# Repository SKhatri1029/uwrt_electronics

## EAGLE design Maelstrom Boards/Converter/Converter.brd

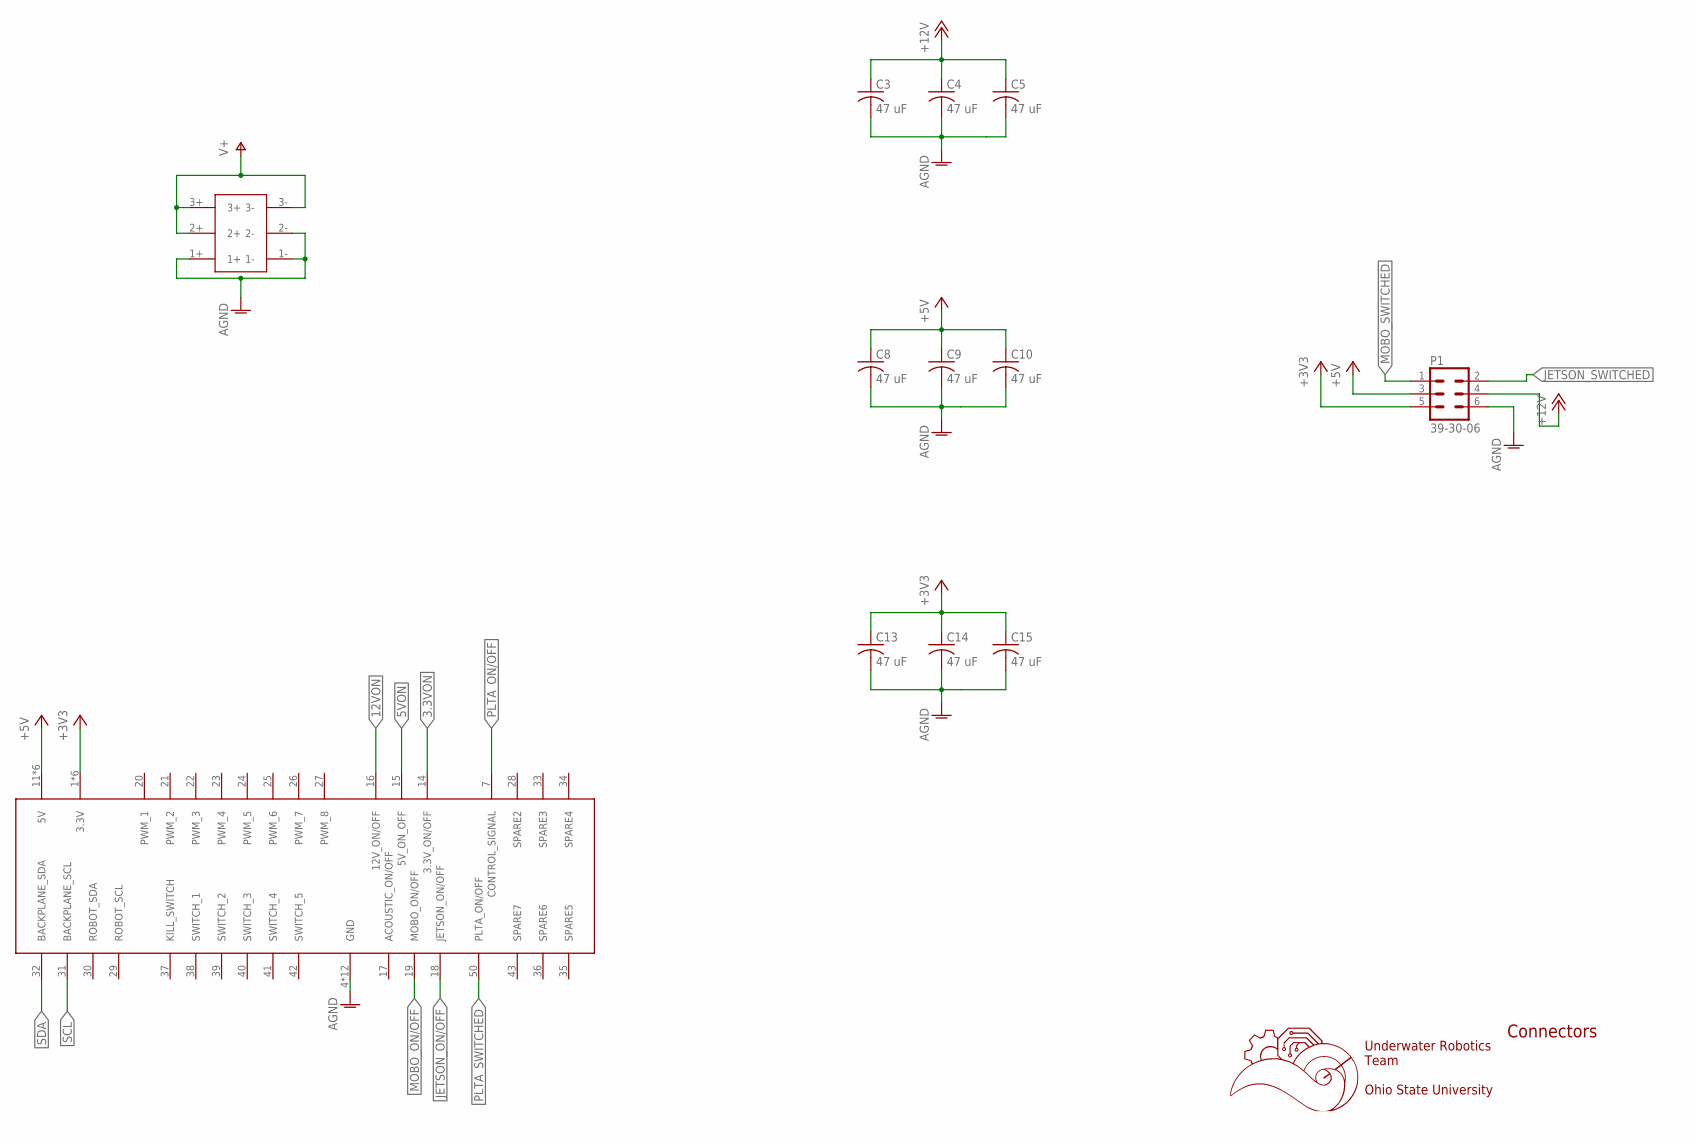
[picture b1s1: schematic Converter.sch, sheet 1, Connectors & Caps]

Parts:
C3, C4, C5, C8, C9, C10, C13, C14, C15: 47 uF; C1206K
P1: 39-30-06; 39-30-?06?
U$1: 5530843-EDGE; 5530843-6-BOARDFINGERS
U$3: 6PIN-VERT; 6PIN_VERT

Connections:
3.3VON: U$1.14 (3.3V_ON/OFF); also elsewhere on the board
5VON: U$1.15 (5V_ON_OFF); also elsewhere on the board
12VON: U$1.16 (12V_ON/OFF); also elsewhere on the board
+3V3: C13.1, C14.1, C15.1, P1.5, U$1.1 (3.3V), U$1.2 (3.3V), U$1.3 (3.3V), U$1.54 (3.3V), U$1.55 (3.3V), U$1.56 (3.3V); also elsewhere on the board
+5V: C8.1, C9.1, C10.1, P1.3, U$1.11 (5V), U$1.12 (5V), U$1.13 (5V), U$1.44 (5V), U$1.45 (5V), U$1.46 (5V); also elsewhere on the board
+12V: C3.1, C4.1, C5.1, P1.4; also elsewhere on the board
AGND: C3.2, C4.2, C5.2, C8.2, C9.2, C10.2, C13.2, C14.2, C15.2, P1.6, U$1.4 (GND), U$1.5 (GND), U$1.6 (GND), U$1.8 (GND), U$1.9 (GND), U$1.10 (GND), U$1.47 (GND), U$1.48 (GND), U$1.49 (GND), U$1.51 (GND), U$1.52 (GND), U$1.53 (GND), U$3.1+, U$3.1-, U$3.2-; also elsewhere on the board
JETSON_ON/OFF: U$1.18 (JETSON_ON/OFF); also elsewhere on the board
JETSON_SWITCHED: P1.2; also elsewhere on the board
MOBO_ON/OFF: U$1.19 (MOBO_ON/OFF); also elsewhere on the board
MOBO_SWITCHED: P1.1; also elsewhere on the board
PLTA_ON/OFF: U$1.7 (CONTROL_SIGNAL); also elsewhere on the board
PLTA_SWITCHED: U$1.50 (PLTA_ON/OFF); also elsewhere on the board
SCL: U$1.31 (BACKPLANE_SCL); also elsewhere on the board
SDA: U$1.32 (BACKPLANE_SDA); also elsewhere on the board
V+: U$3.2+, U$3.3+, U$3.3-; also elsewhere on the board

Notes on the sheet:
Underwater Robotics Team Ohio State University
Connectors

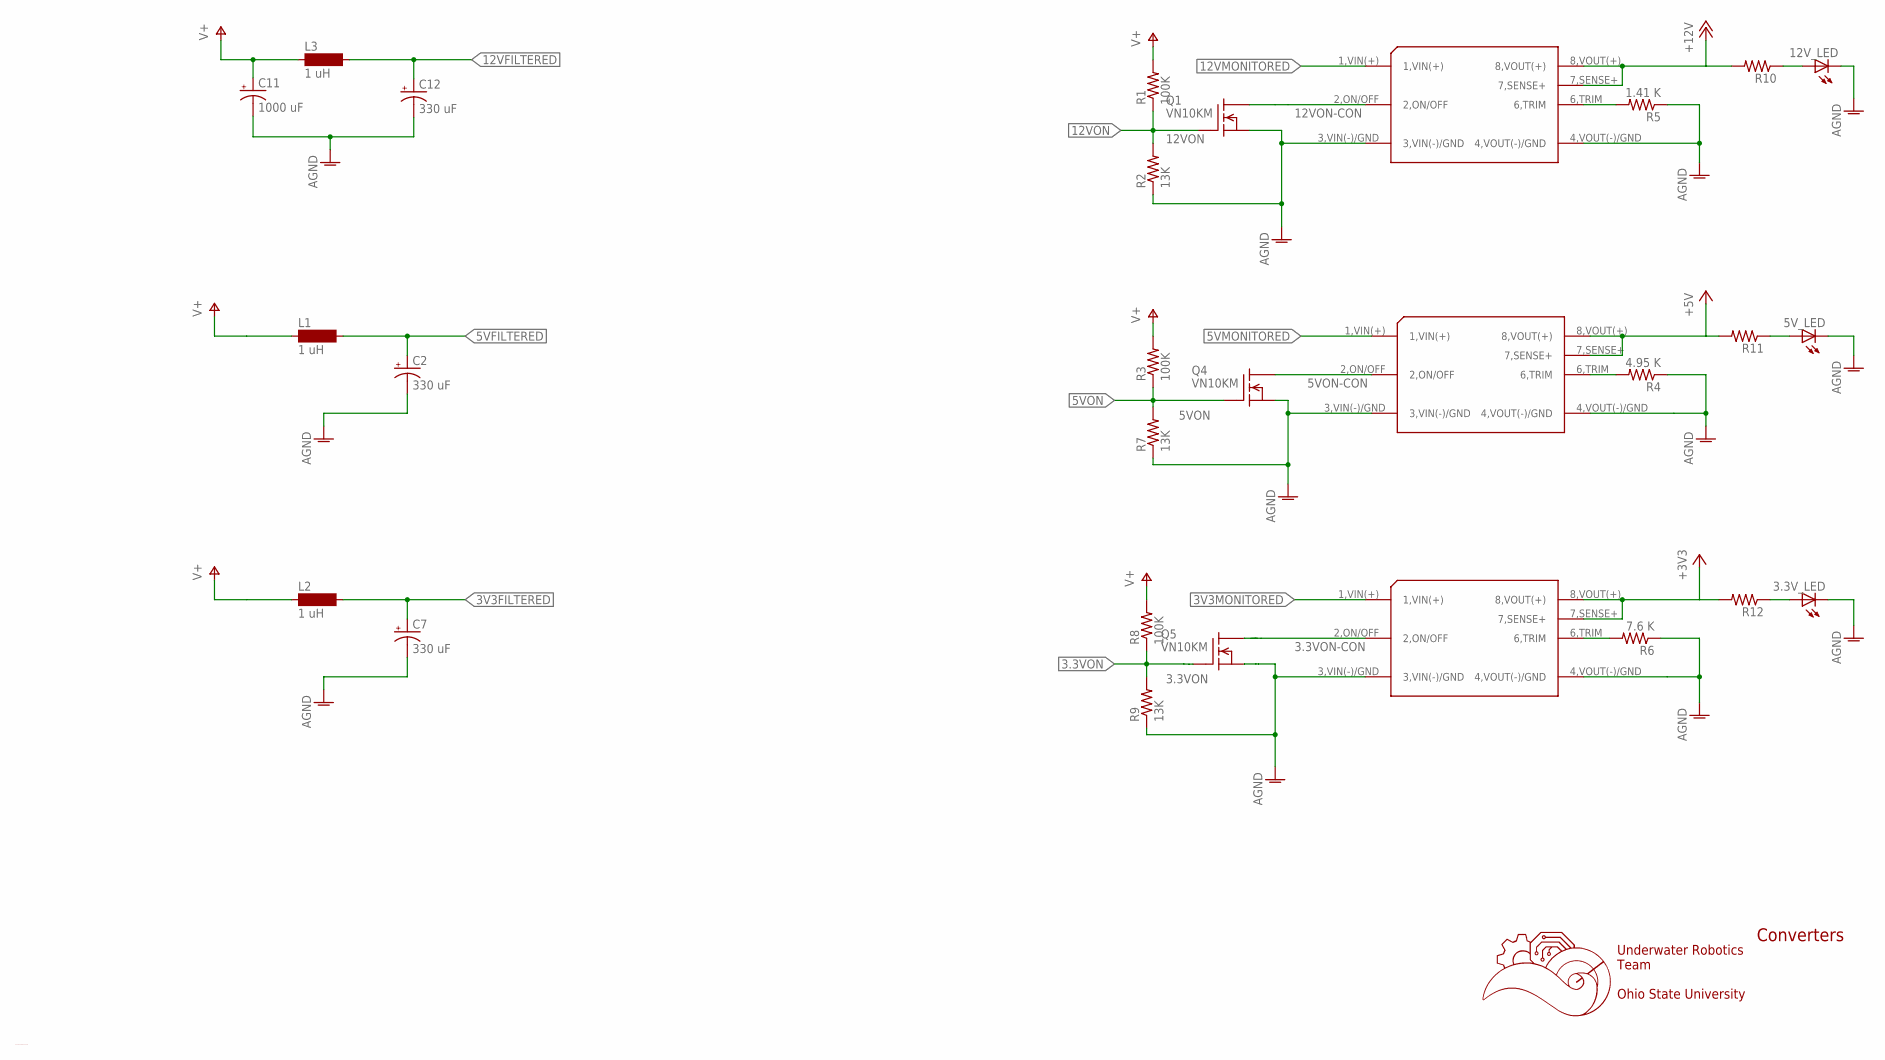
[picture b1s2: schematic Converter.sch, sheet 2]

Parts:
3.3VCONVERTER, 5VCONVERTER, 12VCONVERTER: CONVERTER
3.3V_LED, 5V_LED, 12V_LED: LEDCHIPLED-0603-TTW; CHIPLED-0603-TTW
C2, C7, C12: 330 uF; E5-10,5
C11: 1000 uF; E5-13
L1, L2, L3: 1 uH; MS85
Q1, Q4, Q5: VN10KM; TO237
R1, R3, R8: 100K; R0603
R2, R7, R9: 13K; R0603
R4: 4.95 K; R0603
R5: 1.41 K; R0603
R6: 7.6 K; R0603
R10, R11, R12: R-US_R0603; R0603

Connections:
3.3VON: Q5.2 (G), R8.1, R9.2; also elsewhere on the board
3.3VON-CON: 3.3VCONVERTER.2,ON/OFF, Q5.1 (D)
3V3FILTERED: C7.+, L2.2; also elsewhere on the board
3V3MONITORED: 3.3VCONVERTER.1,VIN(+); also elsewhere on the board
5VFILTERED: C2.+, L1.2; also elsewhere on the board
5VMONITORED: 5VCONVERTER.1,VIN(+); also elsewhere on the board
5VON: Q4.2 (G), R3.1, R7.2; also elsewhere on the board
5VON-CON: 5VCONVERTER.2,ON/OFF, Q4.1 (D)
12VFILTERED: C12.+, L3.2; also elsewhere on the board
12VMONITORED: 12VCONVERTER.1,VIN(+); also elsewhere on the board
12VON: Q1.2 (G), R1.1, R2.2; also elsewhere on the board
12VON-CON: 12VCONVERTER.2,ON/OFF, Q1.1 (D)
+3V3: 3.3VCONVERTER.7,SENSE+, 3.3VCONVERTER.8,VOUT(+), R12.2; also elsewhere on the board
+5V: 5VCONVERTER.7,SENSE+, 5VCONVERTER.8,VOUT(+), R11.2; also elsewhere on the board
+12V: 12VCONVERTER.7,SENSE+, 12VCONVERTER.8,VOUT(+), R10.2; also elsewhere on the board
AGND: 3.3VCONVERTER.3,VIN(-)/GND, 3.3VCONVERTER.4,VOUT(-)/GND, 3.3V_LED.C@1 (C), 5VCONVERTER.3,VIN(-)/GND, 5VCONVERTER.4,VOUT(-)/GND, 5V_LED.C@1 (C), 12VCONVERTER.3,VIN(-)/GND, 12VCONVERTER.4,VOUT(-)/GND, 12V_LED.C@1 (C), C2.-, C7.-, C11.-, C12.-, Q1.3 (S), Q4.3 (S), Q5.3 (S), R2.1, R4.1, R5.1, R6.1, R7.1, R9.1; also elsewhere on the board
unnamed: 12VCONVERTER.6,TRIM, R5.2
unnamed: 5VCONVERTER.6,TRIM, R4.2
unnamed: 3.3VCONVERTER.6,TRIM, R6.2
unnamed: 12V_LED.A@1 (A), R10.1
unnamed: 5V_LED.A@1 (A), R11.1
unnamed: 3.3V_LED.A@1 (A), R12.1
V+: C11.+, L1.1, L2.1, L3.1, R1.2, R3.2, R8.2; also elsewhere on the board

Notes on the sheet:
C:/Users/blain/Downloads/Black and White.bmp
Underwater Robotics Team Ohio State University
Converters

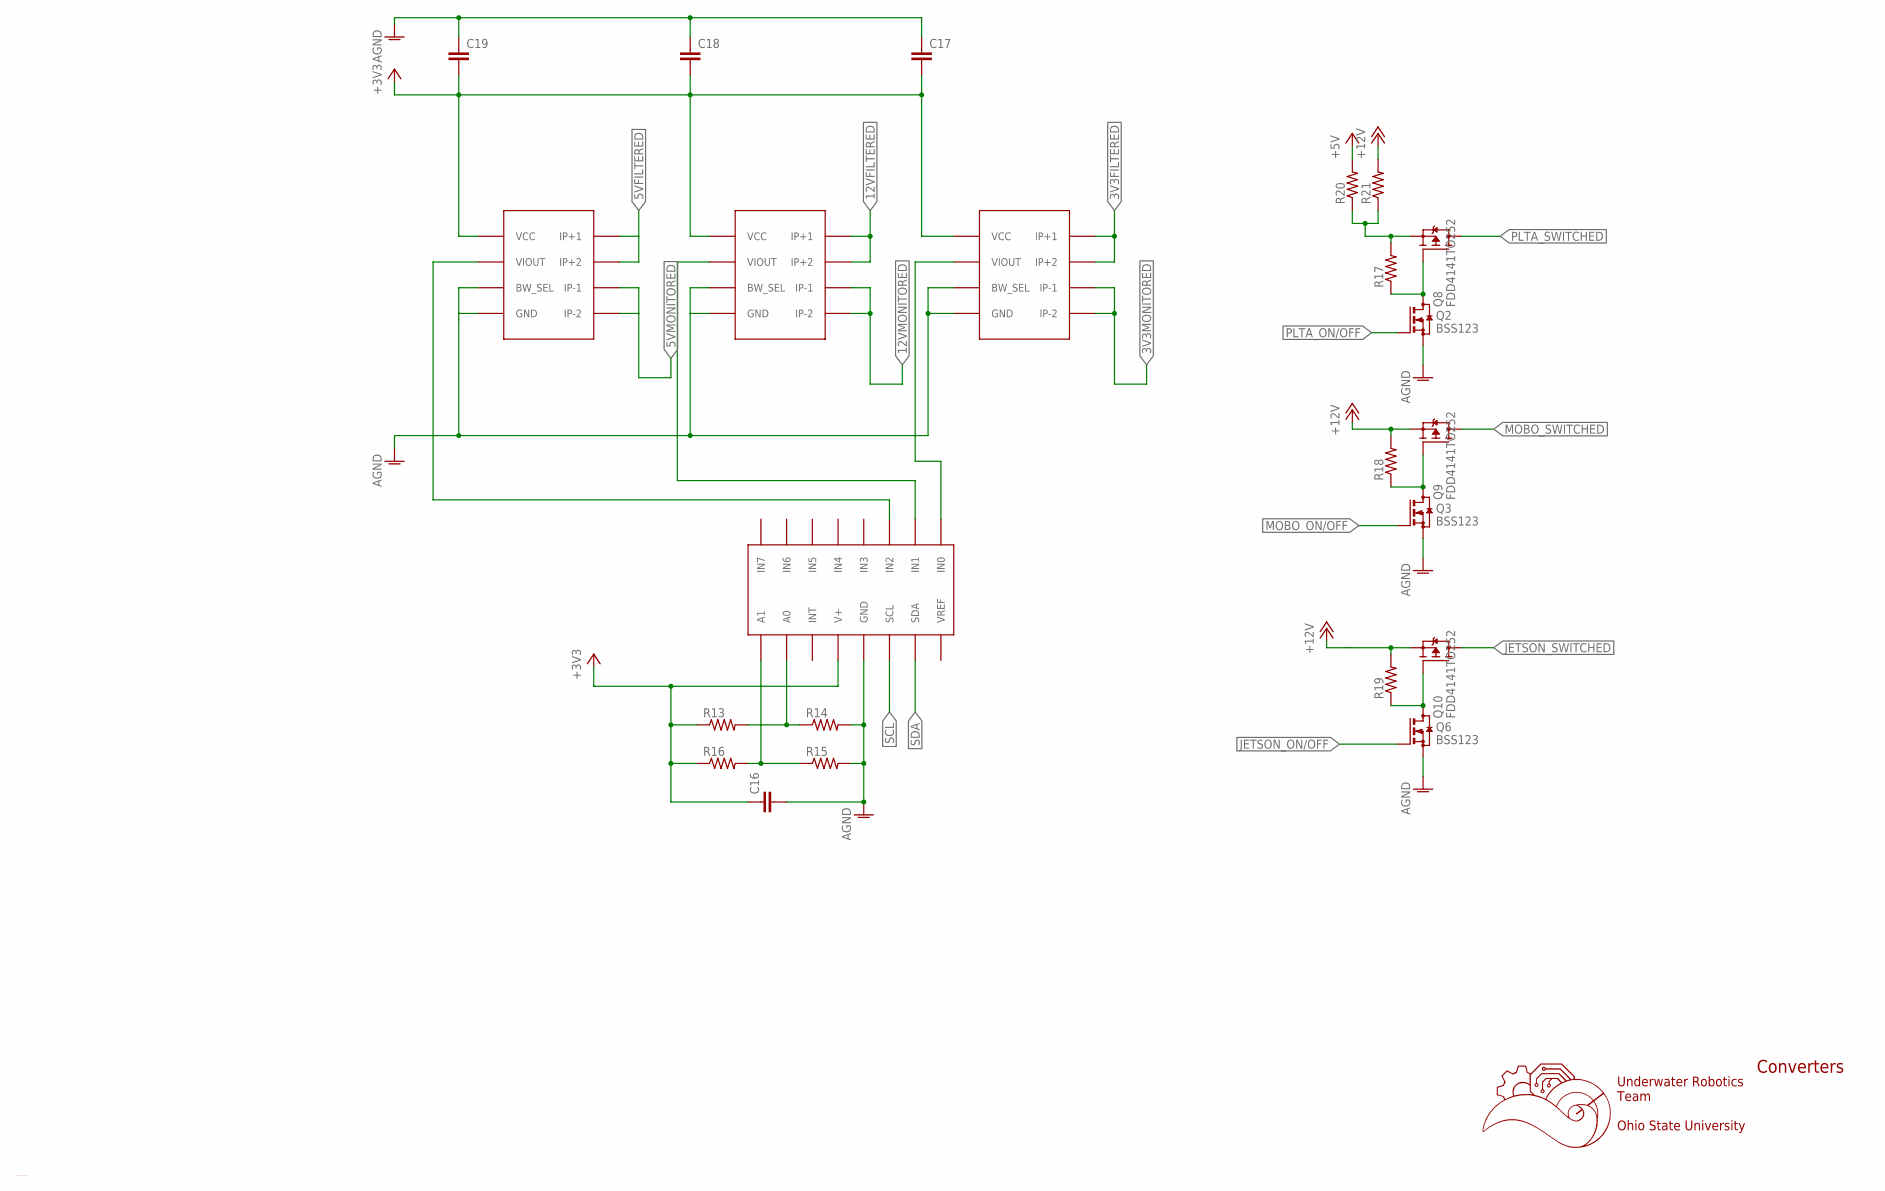
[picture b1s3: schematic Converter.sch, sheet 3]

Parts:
1C, 1C1, 1C2: ACS722; SOIC-8
C16, C17, C18, C19: C-EUC0603; C0603
Q2, Q3, Q6: BSS123; SOT23
Q8, Q9, Q10: FDD4141TO252; TO252
R13, R14, R15, R16, R17, R18, R19, R20: R-US_R0603; R0603
R21: R-US_M2309; M2309
U$2: ADC128D818; TSSOP-16

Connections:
3V3FILTERED: 1C2.IP+1, 1C2.IP+2; also elsewhere on the board
3V3MONITORED: 1C2.IP-1, 1C2.IP-2; also elsewhere on the board
5VFILTERED: 1C.IP+1, 1C.IP+2; also elsewhere on the board
5VMONITORED: 1C.IP-1, 1C.IP-2; also elsewhere on the board
12VFILTERED: 1C1.IP+1, 1C1.IP+2; also elsewhere on the board
12VMONITORED: 1C1.IP-1, 1C1.IP-2; also elsewhere on the board
+3V3: 1C.VCC, 1C1.VCC, 1C2.VCC, C16.1, C17.2, C18.2, C19.2, R13.1, R16.1, U$2.V+; also elsewhere on the board
+5V: R20.2; also elsewhere on the board
+12V: Q9.2 (S), Q10.2 (S), R18.2, R19.2, R21.2; also elsewhere on the board
AGND: 1C.BW_SEL, 1C.GND, 1C1.BW_SEL, 1C1.GND, 1C2.BW_SEL, 1C2.GND, C16.2, C17.1, C18.1, C19.1, Q2.2 (S), Q3.2 (S), Q6.2 (S), R14.2, R15.2, U$2.GND; also elsewhere on the board
JETSON_ON/OFF: Q6.1 (G); also elsewhere on the board
JETSON_SWITCHED: Q10.3 (D); also elsewhere on the board
MOBO_ON/OFF: Q3.1 (G); also elsewhere on the board
MOBO_SWITCHED: Q9.3 (D); also elsewhere on the board
unnamed: Q2.3 (D), Q8.1 (G), R17.1
unnamed: Q3.3 (D), Q9.1 (G), R18.1
unnamed: Q8.2 (S), R17.2, R20.1, R21.1
unnamed: 1C.VIOUT, U$2.IN2
unnamed: 1C1.VIOUT, U$2.IN1
unnamed: 1C2.VIOUT, U$2.IN0
unnamed: Q6.3 (D), Q10.1 (G), R19.1
unnamed: R13.2, R14.1, U$2.A0
unnamed: R15.1, R16.2, U$2.A1
PLTA_ON/OFF: Q2.1 (G); also elsewhere on the board
PLTA_SWITCHED: Q8.3 (D); also elsewhere on the board
SCL: U$2.SCL; also elsewhere on the board
SDA: U$2.SDA; also elsewhere on the board

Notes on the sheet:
C:/Users/blain/Downloads/Black and White.bmp
Underwater Robotics Team Ohio State University
Converters

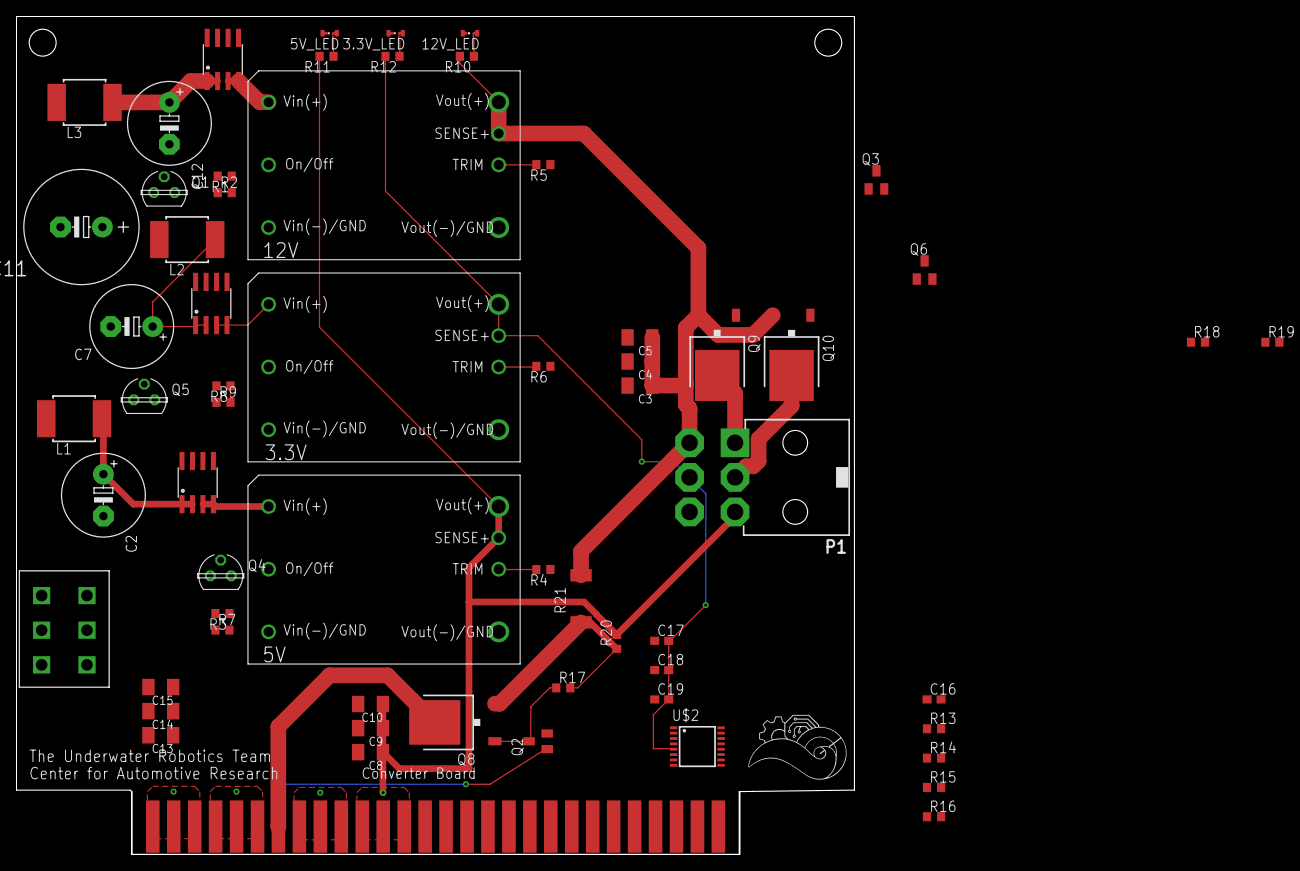
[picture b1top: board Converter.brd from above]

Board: 2 copper layers, 101.6 x 101.6 mm, 63 parts (0 on the bottom side), 40 nets.

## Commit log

2019-02-03 Began routing on converter board
2019-02-17 Converter board completed

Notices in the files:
parts and their libraries:
con-molex-mini-fit: Copyright (C) 2011, Bob Starr
